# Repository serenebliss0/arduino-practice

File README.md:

# Arduino & Electronics Practice Repository

Welcome to my electronics learning journey! This repository contains both **Arduino microcontroller projects** and **pure electronic circuits** (without microcontrollers). Whether you're interested in programming or hardware design, you'll find projects here to expand your skills.

## 📁 Repository Structure

```
arduino-practice/
├── projects/               # All Arduino projects organized by category
│   ├── 01-basics/         # Fundamental Arduino concepts
│   ├── 02-sensors/        # Projects involving sensors
│   ├── 03-actuators/      # Projects with motors, servos, etc.
│   ├── 04-communication/  # Serial, I2C, SPI, Bluetooth, WiFi projects
│   ├── 05-displays/       # LCD, LED matrix, OLED projects
│   └── 06-advanced/       # Complex projects combining multiple concepts
|   └── 07-esp32           # ESP32 Centric projects
├── circuits/              # Pure electronic circuits (no microcontroller)
│   ├── 01-beginner/       # Basic circuits with ICs and transistors
│   ├── 02-intermediate/   # Multi-IC designs and complex logic
│   ├── 03-advanced/       # Advanced analog and digital circuits
│   └── schematics/        # Reference designs and datasheets
├── resources/             # Helpful resources, datasheets, and references
└── templates/             # Project templates and boilerplate code
```

## 🚀 Getting Started

### Prerequisites
- Arduino IDE (or Arduino CLI)
- Arduino board (Uno, Nano, Mega, etc.)
- USB cable for programming
- Basic electronic components (LEDs, resistors, breadboard, jumper wires)

### Setting Up
1. Install the [Arduino IDE](https://www.arduino.cc/en/software)
2. Connect your Arduino board via USB
3. Select the correct board and port in Arduino IDE
4. Open any project sketch (.ino file) and upload to your board

## 📚 Project Categories

### 01 - Basics
Learn fundamental Arduino concepts:
- Digital I/O (LEDs, buttons)
- Analog I/O (potentiometers, analog sensors)
- PWM (fading LEDs, simple motor control)
- Timing and delays
- Serial communication basics

### 02 - Sensors
Work with various sensors:
- Temperature sensors (DHT11, DHT22, LM35)
- Motion sensors (PIR, ultrasonic)
- Light sensors (LDR, photoresistor)
- Sound sensors
- Gas and smoke sensors

### 03 - Actuators
Control physical outputs:
- DC motors and motor drivers
- Servo motors
- Stepper motors
- Relays and solenoids
- Buzzers and speakers

### 04 - Communication
Connect and communicate:
- Serial (UART) communication
- I2C protocol
- SPI protocol
- Bluetooth modules (HC-05, HC-06)
- WiFi modules (ESP8266, ESP32)
- RF modules

### 05 - Displays
Visual output devices:
- 7-segment displays
- LCD displays (16x2, 20x4)
- OLED displays
- LED matrices
- RGB LEDs and LED strips

### 06 - Advanced
Complex integrated projects:
- IoT projects
- Data logging
- Home automation
- Robotics
- Multi-sensor systems

### 07- ESP32

ESP32 Centric projects:
 - Web Servers
 - Bluetooth Low Energy (LE)
 - WiFi Scanners
 - More IoT projects
 - OTA Updates

---

## ⚡ Electronic Circuits (No Microcontroller)

Learn electronics fundamentals by building circuits using ICs, transistors, and discrete components - **no programming required!** Perfect for understanding how hardware works at a deeper level.

### What's Included:
- **32+ Circuit Projects**: From beginner to advanced
- **Practical Learning**: 555 timers, op-amps, logic gates, counters, and more
- **Real Applications**: Amplifiers, power supplies, oscillators, sensors
- **Hardware Focus**: Pure analog and digital circuit design

### Why Learn Circuit Design?
- 🔹 **Understand Electronics Deeply**: See how components work together
- 🔹 **No Programming Needed**: Focus purely on hardware
- 🔹 **Complement Arduino Skills**: Better understand what Arduino does internally
- 🔹 **Build Useful Tools**: Power supplies, testers, amplifiers
- 🔹 **Lower Power**: Many circuits are more efficient than microcontrollers

### Circuit Categories:

#### Beginner (7 Projects)
- 555 Timer LED Blinker
- Dark-Activated LED (transistor switch)
- LED Chaser/Sequencer (4017 IC)
- Simple Audio Amplifier (LM386)
- Touch Switch
- And more!

#### Intermediate (12 Projects)
- SR Latch (Set-Reset Flip-Flop)
- Clap Switch (sound-activated)
- Adjustable Power Supply (LM317)
- Infrared Proximity Sensor
- Motor Speed Controller (PWM)
- Water Level Indicator
- Electronic Metronome (adjustable BPM)
- Capacitance Tester (identify unknown capacitors)
- LED Bar Graph Voltmeter
- And more!

#### Advanced (13 Projects)
- Function Generator (sine, square, triangle waves)
- Security Alarm System
- Digital Dice with 7-segment display
- Traffic Light Controller
- Stepper Motor Driver
- Temperature-Controlled Fan
- VU Meter (Audio Level Indicator)
- Infrared Remote Control System
- DC-DC Boost Converter (switch-mode power supply)
- And more!

### 📚 Full Documentation
For complete project descriptions, component lists, and learning resources:
- **[CIRCUITS.md](CIRCUITS.md)** - Comprehensive guide to all circuit projects
- **[circuits/README.md](circuits/README.md)** - Quick navigation and tips

### Getting Started with Circuits
1. Start with the 555 Timer LED Blinker (beginner)
2. Build the SR Latch to understand digital memory
3. Try an audio amplifier or LED chaser
4. Gradually move to intermediate and advanced projects

**Essential Component**: Get a **multimeter** if you don't have one - it's absolutely crucial for circuit building and debugging!

---

## 📝 How to Add a New Project

1. Choose the appropriate category folder
2. Create a new folder with a descriptive name (e.g., `blink-led`, `ultrasonic-distance`)
3. Add your Arduino sketch (.ino file)
4. Include a README.md with:
   - Project description
   - Components list
   - Circuit diagram or wiring instructions
   - Code explanation
   - Photos/videos of the working project (optional)

## 🛠️ Project Template

See the `templates/` folder for a basic project structure template.

## 📖 Resources

The `resources/` folder contains:
- Component datasheets
- Arduino cheat sheets
- Circuit diagrams
- Useful links and tutorials

## 💡 Need Project Ideas?

### Arduino Projects
Check out **[PROJECT_SUGGESTIONS.md](PROJECT_SUGGESTIONS.md)** for 50+ Arduino project ideas organized by difficulty level and category! Includes:
- Easy starter projects to build on what you've learned
- Intermediate projects combining multiple components
- Advanced IoT, robotics, and automation projects
- Recommended learning path
- Components shopping list

### Circuit Projects (No Microcontroller)
Check out **[CIRCUITS.md](CIRCUITS.md)** for 32+ pure electronics projects! Includes:
- Beginner circuits with 555 timers and basic ICs
- Intermediate circuits with op-amps and logic gates
- Advanced circuits with multiple ICs and complex designs
- Essential components guide
- Circuit design tips and learning resources

## 🛒 Shopping List

Need to buy parts? Check out **[SHOPPING_LIST.md](SHOPPING_LIST.md)** for a complete, consolidated shopping list covering **every component** needed for:
- All 32+ circuit projects (no microcontroller)
- All Arduino microcontroller projects
- All ESP32 projects

Organized by category (resistors, capacitors, ICs, sensors, etc.) with quantities, cost estimates, and sourcing tips so you can buy everything in one go.

## 🔗 Useful Links

- [Arduino Official Website](https://www.arduino.cc/)
- [Arduino Reference](https://www.arduino.cc/reference/en/)
- [Arduino Project Hub](https://create.arduino.cc/projecthub)
- [Arduino Forum](https://forum.arduino.cc/)

## 📜 License

This project is licensed under the MIT License - see the [LICENSE](LICENSE) file for details.

## 🤝 Contributing

This is a personal learning repository, but feel free to:
- Suggest improvements
- Share ideas for new projects
- Report issues or bugs in the code
- Visit the [Issues](https://github.com/serenebliss0/arduino-practice/issues) tab to suggest your idea or report an issue! 

---

Happy tinkering! 🎉

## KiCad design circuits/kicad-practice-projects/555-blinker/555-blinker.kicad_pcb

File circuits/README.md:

# 🔌 Circuits Directory

This directory contains electronic circuit projects that **don't require Arduino or any microcontroller**. These are pure hardware designs using ICs, transistors, and other discrete components.

## 📁 Directory Structure

```
circuits/
├── README.md                    # This file - navigation and overview
├── 01-beginner/                 # Basic circuits (7 projects)
│   ├── 01-555-timer-led-blinker/     ✅
│   ├── 02-simple-led-flashlight/     ✅
│   ├── 03-dark-activated-led/        ✅
│   ├── 04-push-button-debouncing/    ✅
│   ├── 05-simple-audio-amplifier/    ✅
│   ├── 06-led-chaser-4017/           ✅
│   └── 07-touch-switch/
├── 02-intermediate/             # Intermediate circuits (8 projects)
│   ├── 08-sr-latch/                  ✅
│   ├── 09-clap-switch/
│   ├── 10-automatic-emergency-light/
│   ├── 11-ir-proximity-sensor/
│   ├── 12-adjustable-power-supply/
│   ├── 13-motor-speed-controller/
│   ├── 14-water-level-indicator/
│   └── 15-bistable-relay/
├── 03-advanced/                 # Advanced circuits (11 projects)
│   ├── 16-digital-dice/
│   ├── 17-security-alarm-system/
│   ├── 18-traffic-light-controller/
│   ├── 19-function-generator/
│   ├── 20-dual-power-supply/
│   ├── 21-temperature-controlled-fan/
│   ├── 22-stepper-motor-driver/
│   ├── 23-digital-logic-probe/
│   ├── 24-analog-volt-ammeter/
│   ├── 25-pwm-motor-controller/
│   └── 26-binary-counter-7segment/
└── schematics/                  # General schematics and reference designs
```

## 🎯 What's in This Section?

### Project Organization
All 26 circuit projects from CIRCUITS.md are now organized into folders by difficulty level! Each project folder contains:
- **README.md**: Full documentation, theory, components, building instructions
- **Circuit files**: Fritzing (.fzz), schematics, and photos (as available)

### Current Status
- ✅ **All 26 project folders created** with documentation
- ✅ **Beginner projects (1-7)**: Complete READMEs with detailed instructions
- ✅ **Intermediate projects (8-9)**: Detailed READMEs, others have basic structure
- ✅ **Advanced projects (16-26)**: Basic structure with references to CIRCUITS.md
- ✅ **Existing circuits moved** to appropriate folders (555 Timer, SR Latch)

### Projects by Category

#### 01-Beginner/
- Basic circuits using LEDs, resistors, and simple ICs
- 555 timer projects
- Transistor switches
- Simple sensor circuits

#### 02-Intermediate/
- Multi-IC designs
- Op-amp circuits
- Counter and sequencer circuits
- Audio and power circuits

#### 03-Advanced/
- Complex state machines
- Multi-stage amplifiers
- Advanced timing circuits
- Power supplies and converters

#### Schematics/
- Reference designs
- Component datasheets
- Common circuit building blocks
- Test and measurement circuits

## 📚 Full Documentation

For complete project ideas, learning resources, and step-by-step guides, see:
- **[CIRCUITS.md](../CIRCUITS.md)** - Comprehensive guide with 26+ circuit projects
  - Beginner projects (7 projects)
  - Intermediate projects (9 projects)
  - Advanced projects (10 projects)
  - Component guides
  - Learning resources
  - Circuit design tips

## 🔨 How to Add New Circuit Projects

### 1. Choose the Right Category
- **Beginner**: Simple circuits with 1-2 ICs or basic transistor circuits
- **Intermediate**: Multi-IC designs, sensor integration, moderate complexity
- **Advanced**: Complex systems, multiple ICs, professional designs

### 2. Create Project Folder
```
circuits/[category]/project-name/
├── project-name.fzz           # Fritzing circuit file
├── schematic.png              # Exported schematic image
├── breadboard.png             # Breadboard layout (optional)
├── README.md                  # Project documentation
└── photos/                    # Working circuit photos
```

### 3. Document Your Circuit
Your README.md should include:

```markdown
# Project Name

## Difficulty: ⭐⭐⭐☆☆

## What You'll Learn
- Key concept 1
- Key concept 2
- Key concept 3

## Components Required
- Component 1 (quantity, specs)
- Component 2 (quantity, specs)
- etc.

## Circuit Description
Explain how the circuit works, what each section does.

## Theory of Operation
Detailed explanation of the circuit's operation.

## Building Instructions
1. Step 1
2. Step 2
3. etc.

## Testing & Troubleshooting
- Expected voltages at test points
- Common issues and solutions
- What to check if it doesn't work

## Photos
Include photos of your working circuit!

## Calculations
Any relevant formulas or calculations.

## Resources
- Links to datasheets
- Reference articles
- Tutorial videos
```

## 🛠️ Essential Tools & Components

### You Have / Likely Have:
- ✅ Breadboard
- ✅ Jumper wires
- ✅ Fritzing software

### Recommended Additions:
- [ ] **Multimeter** - Absolutely essential for circuit building!
- [ ] 555 Timer ICs - Most versatile IC ever
- [ ] Op-Amps (LM358 or LM324)
- [ ] Logic ICs (CD4017, CD4011)
- [ ] Basic transistors (BC547, TIP122)
- [ ] Assorted resistors and capacitors
- [ ] Power supply (breadboard power supply recommended)

## 📖 Getting Started

### New to Circuit Design?
1. Read [CIRCUITS.md](../CIRCUITS.md) for full project list
2. Start with beginner projects (#1-7)
3. Build the 555 Timer LED Blinker first
4. Learn to read datasheets
5. Practice on breadboard before soldering

### From Arduino to Circuits?
Great! You already understand:
- ✅ Basic electronics (voltage, current, resistance)
- ✅ Component identification
- ✅ How to use a breadboard
- ✅ Reading circuit diagrams

Now learn:
- 🔹 How ICs work at the hardware level
- 🔹 Analog circuit design
- 🔹 Timing and oscillator circuits
- 🔹 Digital logic without code
- 🔹 Power supply design

## 🎓 Learning Path

### Week 1-2: Start Simple
1. Build LED Blinker (555 timer)
2. Build SR Latch (understand flip-flops)
3. Experiment with component values

### Week 3-4: Add More ICs
4. LED Chaser (4017 counter)
5. Dark-Activated LED (transistor switch)
6. Touch Switch (logic gates)

### Week 5+: Intermediate & Beyond
Choose projects that interest you from CIRCUITS.md!

## 🔗 Useful Resources

### Circuit Simulators (Test Before Building!)
- **Falstad Circuit Simulator** - Browser-based, instant feedback
- **CircuitLab** - Online schematic capture and simulation
- **LTspice** - Professional SPICE simulator (free)

### Learning Sites
- **All About Circuits** - Free textbooks and tutorials
- **Electronics Tutorials** - Comprehensive circuit theory
- **EEVblog** - YouTube channel with electronics content

### Datasheets
Always check datasheets at:
- Manufacturer websites
- AllDataSheet.com
- DataSheetCatalog.com

## ⚡ Safety Reminders

### Always:
- ✅ Double-check polarity of electrolytic capacitors
- ✅ Verify IC pin 1 orientation (dot or notch)
- ✅ Use appropriate resistors for LEDs
- ✅ Add flyback diodes for inductive loads
- ✅ Check power supply voltage before connecting

### Never:
- ❌ Connect power backwards
- ❌ Exceed maximum ratings
- ❌ Touch live AC circuits
- ❌ Work on circuits while powered
- ❌ Skip the datasheet!

### For AC Projects:
- ⚠️ **DANGER**: AC voltage can be lethal
- ⚠️ Test with DC first
- ⚠️ Use proper insulation
- ⚠️ Turn off power at breaker
- ⚠️ Consider hiring an electrician for permanent installations

## 💡 Quick Tips

### Breadboarding:
- Use color-coded wires (Red=+5V, Black=GND, others=signals)
- Keep wires flat and organized
- Add 100nF bypass capacitors near each IC
- Route power rails carefully

### Debugging:
- Start with power - verify voltages first
- Check all connections visually
- Measure voltages at each IC pin
- Use LED indicators to trace signals
- Verify IC orientations (pin 1!)

### Components:
- Resistor color codes: Google "resistor color code calculator"
- Capacitor polarity: Longer leg = positive (for electrolytics)
- LED polarity: Longer leg = anode (+)
- IC pinout: Pin 1 has dot or notch, count counter-clockwise

## 🎯 Project Ideas by Goal

### Want to Learn Timing?
- 555 Timer LED Blinker
- LED Chaser (4017 + 555)
- PWM Motor Controller

### Want to Learn Logic?
- SR Latch
- Touch Switch
- Digital Dice
- Traffic Light Controller

### Want to Learn Analog?
- Audio Amplifier (LM386)
- Function Generator (Op-amps)
- Temperature-Controlled Fan
- Adjustable Power Supply

### Want to Build Something Useful?
- Clap Switch
- Emergency Light
- Water Level Indicator
- Security Alarm System

## 📝 Contributing

This is a personal learning repository, but you can:
- Suggest circuit project ideas
- Share improvements to existing circuits
- Report errors in schematics or documentation
- Recommend useful components or resources

---

## 🚀 Next Steps

1. **Read** [CIRCUITS.md](../CIRCUITS.md) for complete project descriptions
2. **Choose** a beginner project to start with
3. **Gather** components you need
4. **Build** on breadboard and document your work
5. **Test** thoroughly and troubleshoot
6. **Save** your Fritzing files here
7. **Document** your learning journey

---

**Remember**: Circuit design is a skill built through practice. Start simple, understand each component, and gradually tackle more complex projects. Every circuit you build adds to your knowledge!

Happy circuit building! ⚡🔧

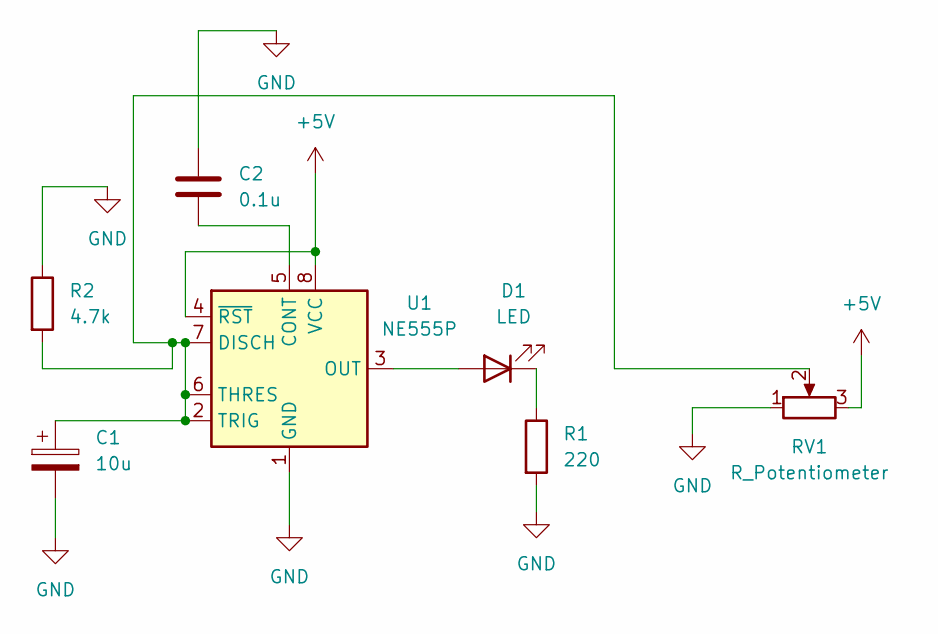
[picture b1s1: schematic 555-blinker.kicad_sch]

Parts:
C1: 10u; CP_Axial_L11.0mm_D6.0mm_P18.00mm_Horizontal
C2: 0.1u; C_Disc_D3.0mm_W1.6mm_P2.50mm
D1: LED; LED_D4.0mm
R1: 220; R_Axial_DIN0309_L9.0mm_D3.2mm_P15.24mm_Horizontal
R2: 4.7k; R_Axial_DIN0309_L9.0mm_D3.2mm_P15.24mm_Horizontal
RV1: R_Potentiometer; Potentiometer_Omeg_PC16BU_Horizontal
U1: NE555P; DIP-8_W7.62mm

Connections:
+5V: RV1.3, U1.4 (~RST), U1.8 (VCC)
GND: C1.2, C2.1, R1.2, R2.1, RV1.1, U1.1 (GND)
unnamed: D1.2 (A), U1.3 (OUT)
unnamed: D1.1 (K), R1.1
unnamed: C2.2, U1.5 (CONT)
unnamed: C1.1, R2.2, RV1.2, U1.2 (TRIG), U1.6 (THRES), U1.7 (DISCH)

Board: 2 copper layers, 7 parts (0 on the bottom side), 6 nets, no tracks yet.

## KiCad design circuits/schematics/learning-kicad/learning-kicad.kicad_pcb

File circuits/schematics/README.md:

# 📐 Schematics and Reference Designs

## Purpose
This directory contains general schematics, reference designs, and circuit building blocks that can be used across multiple projects.

## Contents

### Reference Circuits
- Common circuit building blocks
- Standard configurations for popular ICs
- Tested and verified designs

### Component Reference
- IC pinout diagrams
- Common component values
- Substitution guides

### Design Templates
- Power supply circuits
- Amplifier stages
- Filter circuits
- Oscillator designs
- Logic gate configurations

## Useful Reference Designs

### Power Supplies
- **5V Regulator (7805)**: Standard configuration with input/output caps
- **Variable Regulator (LM317)**: Adjustable voltage with calculation formulas
- **Dual Supply (±12V)**: Center-tapped transformer design

### Amplifiers
- **Common Emitter Amplifier**: Basic transistor amplifier stage
- **Op-Amp Configurations**: Inverting, non-inverting, differential
- **Audio Amp (LM386)**: Standard audio amplifier circuit

### Oscillators and Timers
- **555 Astable**: Basic oscillator with frequency calculations
- **555 Monostable**: One-shot timer configuration
- **Crystal Oscillator**: Precision timing circuits

### Logic and Digital
- **Debounce Circuit**: Clean switch inputs
- **SR Latch**: Basic flip-flop using gates
- **Clock Divider**: Using counter ICs

### Motor Control
- **H-Bridge**: Bidirectional motor control
- **Stepper Driver**: Unipolar and bipolar configurations
- **PWM Controller**: Variable speed control

### Sensors and Interfaces
- **LDR Light Sensor**: Light detection with threshold
- **Temperature Sensor**: LM35 interfacing
- **IR Transmitter/Receiver**: Proximity detection

## Adding Schematics

### File Formats
- **Fritzing (.fzz)**: For breadboard and schematic views
- **PDF**: For easy viewing and printing
- **PNG/JPG**: For quick reference
- **KiCad files**: For PCB design

### Naming Convention
```
[function]-[ic/component]-[variant].ext

Examples:
- 555-astable-1khz.fzz
- lm386-amplifier-min-gain.pdf
- 7805-regulator-standard.png
```

### Documentation
Each schematic should include:
1. **Title and description**
2. **Component values**
3. **Key formulas** (if applicable)
4. **Input/output specifications**
5. **Notes and warnings**

## Common IC Pinouts

### 555 Timer (8-pin DIP)
```
    +--U--+
GND |1   8| VCC
TRG |2   7| DIS
OUT |3   6| THR
RST |4   5| CTL
    +-----+
```

### LM358/LM324 Op-Amp
```
LM358 (Dual)        LM324 (Quad)
    +--U--+             +--U--+
1O  |1   8| VCC     1O  |1  14| 4O
1-  |2   7| 2O      1-  |2  13| 4-
1+  |3   6| 2-      1+  |3  12| 4+
GND |4   5| 2+      VCC |4  11| GND
    +-----+         2O  |5  10| 3+
                    2-  |6   9| 3-
                    2+  |7   8| 3O
                        +------+
```

### CD4017 Decade Counter
```
     +--U--+
 Q5  |1  16| VCC
 Q1  |2  15| RST
 Q0  |3  14| CLK
 Q2  |4  13| EN
 Q6  |5  12| OUT
 Q7  |6  11| Q4
 Q3  |7  10| Q8
 GND |8   9| Q9
     +------+
```

## Standard Component Values

### Resistors (E12 Series)
10, 12, 15, 18, 22, 27, 33, 39, 47, 56, 68, 82 (×10ⁿ)

Common values: 220Ω, 1kΩ, 10kΩ, 100kΩ, 1MΩ

### Capacitors
**Ceramic (nF)**: 1, 10, 100, 470
**Electrolytic (µF)**: 1, 10, 100, 470, 1000

### LEDs
- Forward Voltage: 1.8-3.6V (depending on color)
- Forward Current: 10-20mA (typical)
- Current Limiting Resistor: 220Ω - 1kΩ

## Circuit Design Tips

### Power Supply Guidelines
1. Always add 100nF bypass capacitor near each IC
2. Use electrolytic caps (10µF-100µF) for bulk filtering
3. Add reverse polarity protection (diode)
4. Calculate power dissipation for regulators
5. Use adequate heatsinks for power components

### Signal Conditioning
1. Use voltage dividers for scaling
2. Add RC filters for noise reduction
3. Buffer high-impedance signals with op-amps
4. Decouple analog and digital grounds

### Protection Circuits
1. Flyback diodes for inductive loads (motors, relays)
2. TVS diodes for ESD protection
3. Fuses for overcurrent protection
4. Zener diodes for voltage clamping

## Testing and Troubleshooting

### Essential Measurements
1. **Power rails**: Verify correct voltages
2. **IC pins**: Check VCC and GND first
3. **Signal paths**: Trace signals with multimeter/oscilloscope
4. **Component values**: Verify with multimeter

### Common Problems
- **No power**: Check connections and battery
- **Intermittent operation**: Loose connections
- **Incorrect output**: Wrong component values
- **Overheating**: Insufficient current limiting or heatsinking

## Resources

### Online Simulators
- **Falstad Circuit Simulator**: https://falstad.com/circuit/
- **CircuitLab**: https://www.circuitlab.com/
- **LTspice**: https://www.analog.com/en/design-center/design-tools-and-calculators/ltspice-simulator.html - Free SPICE simulator by Analog Devices

### Reference Websites
- **All About Circuits**: https://www.allaboutcircuits.com/
- **Electronics Tutorials**: https://www.electronics-tutorials.ws/
- **TI Precision Labs**: Training videos from Texas Instruments

### Datasheet Sources
- Manufacturer websites (TI, Analog, ON Semi, etc.)
- **AllDataSheet**: https://www.alldatasheet.com/
- **DataSheetCatalog**: https://www.datasheetcatalog.com/

## Contributing

### Adding New Schematics
1. Create clear, well-documented schematic
2. Test circuit on breadboard
3. Export in multiple formats (Fritzing, PDF, PNG)
4. Add README with full documentation
5. Include component list and values
6. Add notes about variations and alternatives

### Quality Guidelines
- ✅ Clean, readable schematic layout
- ✅ All components labeled with values
- ✅ Clear input/output labels
- ✅ Include test points
- ✅ Add notes for critical values
- ✅ Specify power requirements

## Safety Reminders

### Low Voltage Circuits (< 30V DC)
- ✅ Generally safe to touch
- ⚠️ Still respect polarity and component ratings

### High Voltage / AC Circuits
- ⚠️ **DANGEROUS** - Can be lethal!
- ⚠️ Never work on live AC circuits
- ⚠️ Use isolated transformers for testing
- ⚠️ Follow electrical codes for permanent installations
- ⚠️ Consider consulting qualified electrician

### Component Safety
- ⚠️ Watch capacitor polarity (can explode!)
- ⚠️ Use heatsinks for power components
- ⚠️ Don't exceed maximum IC voltages
- ⚠️ Add flyback diodes for relays/motors
- ⚠️ Fuse all power supplies

---

**Status**: 📋 Awaiting reference schematics and designs
**Last Updated**: December 2024

Build with confidence! 📐⚡

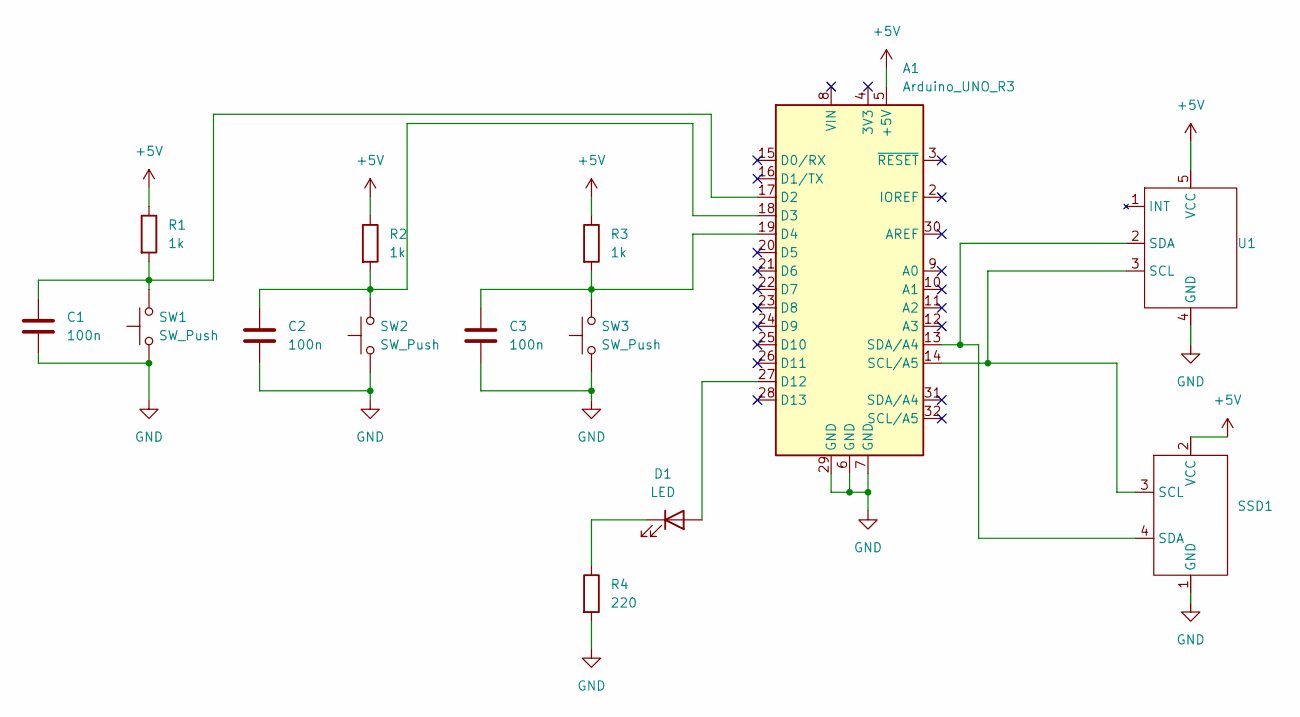
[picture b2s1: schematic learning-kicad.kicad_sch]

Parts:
A1: Arduino_UNO_R3
C1, C2, C3: 100n; C_Disc_D4.7mm_W2.5mm_P5.00mm
D1: LED; LED_D5.0mm
R1, R2, R3: 1k; R_Axial_DIN0207_L6.3mm_D2.5mm_P7.62mm_Horizontal
R4: 220; R_Axial_DIN0207_L6.3mm_D2.5mm_P7.62mm_Horizontal
SSD1: SSD1306
SW1, SW2, SW3: SW_Push; SW_PUSH_6mm
U1: MAX30102

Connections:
+5V: A1.5 (+5V), R1.1, R2.1, R3.1, SSD1.2 (VCC), U1.5 (VCC)
GND: A1.6 (GND), A1.7 (GND), A1.29 (GND), C1.2, C2.2, C3.2, R4.2, SSD1.1 (GND), SW1.1, SW2.1, SW3.1, U1.4 (GND)
unnamed: A1.17 (D2), C1.1, R1.2, SW1.2
unnamed: A1.18 (D3), C2.1, R2.2, SW2.2
unnamed: A1.19 (D4), C3.1, R3.2, SW3.2
unnamed: A1.27 (D12), D1.2 (A)
unnamed: D1.1 (K), R4.1
unnamed: A1.14 (SCL/A5), SSD1.3 (SCL), U1.3 (SCL)
unnamed: A1.13 (SDA/A4), SSD1.4 (SDA), U1.2 (SDA)

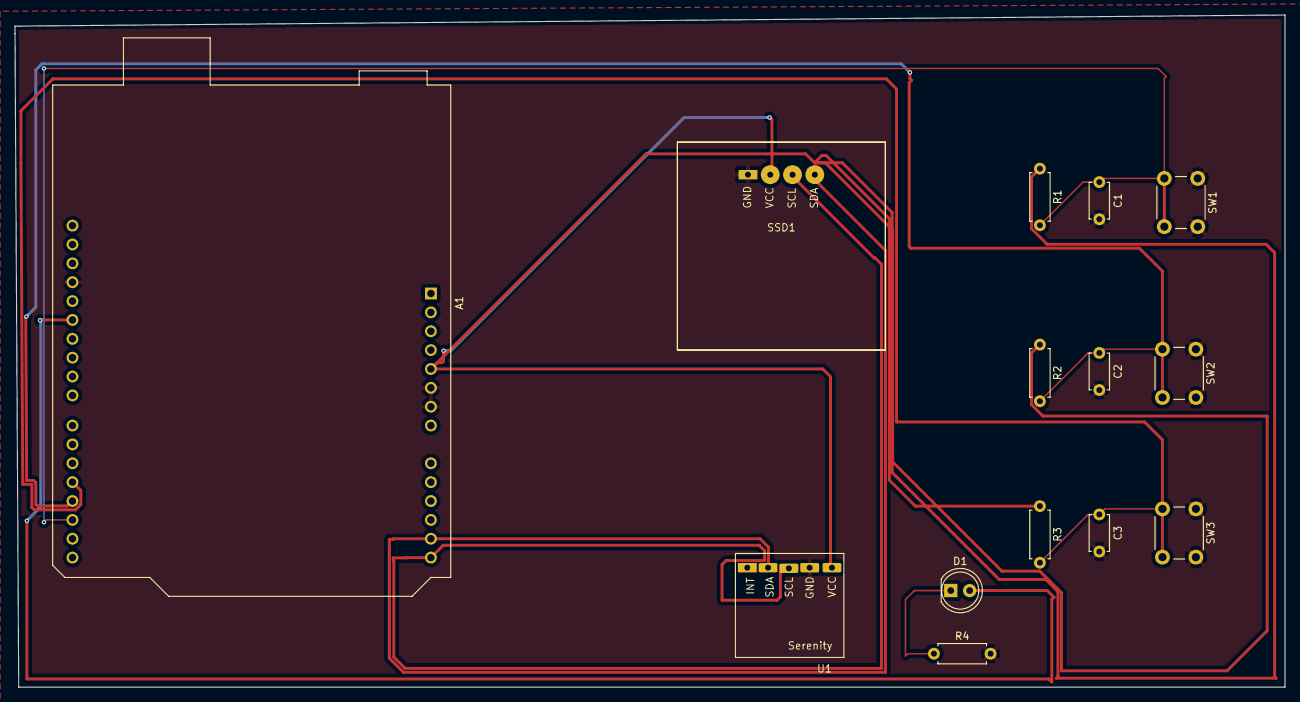
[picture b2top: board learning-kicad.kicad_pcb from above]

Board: 4 copper layers, 171.0 x 90.5 mm, 14 parts (0 on the bottom side), 9 nets.

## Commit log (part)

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2025-12-02 Initial plan
2025-12-02 Add comprehensive Arduino project organization structure
2025-12-02 Address code review feedback on documentation
2025-12-05 Added new projects
2025-12-07 Add comprehensive project suggestions with 50+ ideas
2025-12-07 Address code review feedback: clarify DHT sensors, safety warnings, I2C adapters, and ESP8266/ESP32
2025-12-07 Final refinements: complete sensor specs and clearer I2C/ESP explanations
2025-12-07 Implemented the Automatic Traffic Lights project using Arduino, featuring LED control based on ambient light detected by a photoresistor.
2025-12-07 Mark Traffic Light System project as completed
2025-12-07 Add new projects: LED arrays, PWM fading, and momentary switch; update project suggestions with completion status
2025-12-09 Add project files for LED Arrays, including code and Fritzing diagram
2025-12-10 Add comprehensive circuits section with 26+ projects
2025-12-11 Create complete circuit project folder structure with 26 projects
2025-12-11 Address code review feedback: fix emoji consistency and add LTspice URL
2025-12-11 Add Heads or Tails project with LED control and random number generation
2025-12-11 Add RGB LED color mixer project with button control and LED toggling
2025-12-13 Refactor code structure for improved readability and maintainability
2025-12-18 Mark RGB LED Color Mixer suggestion as completed
2025-12-18 Add RGB LED color mixer project with potentiometer control
2025-12-25 Finished dark activated led project
2025-12-25 Finished push button debouncing project
2025-12-26 Add simple reaction time game project
2025-12-27 Mark projects as completed in suggestions
2025-12-27 Update Easy Projects section with a checkmark
2025-12-29 Add DHT11 temperature and humidity sensor project with LCD display
    - Implemented a temperature sensor project using DHT11 sensor
    - Integrated 16x2 LCD display for real-time temperature and humidity readings
    - Established I2C communication for the LCD module
    - Included necessary libraries: Wire, LiquidCrystal_I2C, and DHTlib
    - Configured pin connections for DHT11 and LCD
    - Displayed temperature in Celsius and humidity percentage on the LCD
2025-12-29 Added a visual ultrasonic-sensor based distance measuring project
2025-12-31 Add comprehensive READMEs for projects 9 (Clap Switch) and 10 (Emergency Light)
2025-12-31 Add comprehensive READMEs for projects 11 (IR Sensor) and 12 (Power Supply)
2025-12-31 Add comprehensive READMEs for projects 13 (Motor Controller) and 14 (Water Level)
2025-12-31 Add comprehensive README for project 15 (Bistable Relay)
2025-12-31 Fix typo in project 15 README
2025-12-31 Add complete README files for projects 16 and 17
2025-12-31 Add complete README for project 18 (Traffic Light Controller)
2025-12-31 Add complete README for project 19 (Function Generator)
2025-12-31 Add complete README for project 20 (Dual Power Supply)
2026-02-06 Finished the LM386 Audio Amplifier project
2026-02-06 Added Audio Amplifier schematic
2026-02-06 Revise project status indicators in README
    Updated project status indicators for clarity.
2026-02-11 Add comprehensive README for ESP32 Email Notifier project
    - Created detailed 5,154-word README for project 05-email-notifier
    - Follows same format as project 04-mqtt-sensor-network
    - Includes all required sections: overview, components, wiring, code explanation, usage
    - Added detailed Gmail App Password setup instructions
    - Included SMTP configurations for Gmail, Outlook, and Yahoo
    - Comprehensive troubleshooting section for common SMTP and email issues
2026-02-11 Add comprehensive README for ESP32 OTA Updates project
2026-02-11 Add comprehensive NTP Clock project README with 5389 words
2026-02-11 Add comprehensive documentation and sketches for ESP32 projects 04-07
2026-02-11 Fix project reference in NTP Clock README
2026-02-11 Fix alignment in printDetailedInfo() function
2026-02-11 Add Project 10: BLE Beacon with comprehensive documentation and Arduino sketch
2026-02-11 Remove Arduino sketch files - keep documentation guides only
2026-02-14 Added new projects for ESP32 and started development on MAUI powered application for controlling via Bluetooth
2026-02-14 Add ESP32 projects section to README
    Added section for ESP32 centric projects with examples.
2026-02-21 Enhance README for LED chaser project
    Updated the README with additional details on the 555 Timer IC configuration, stability fixes, and circuit status.
2026-02-21 Update circuit status to completed
2026-02-21 Milestone Update – Embedded Systems Journey
    Completed:
    - CD4017 LED Chaser
    - ESP32 Web Server
    Started:
    - Learning KiCad (PCB design)
    - Google Assistant Smart Speaker project
2026-02-21 Removed unneccessary files
2026-02-21 Removed broken project
2026-02-22 Revise README for SR Latch circuit
    Updated the README to enhance clarity on SR Latch functionality and wiring instructions.
2026-02-22 Add SR Latch circuit schematic and started intermediate section in the circuits directory
2026-02-22 Added datasheet for CD4011
2026-02-25 Add 6 new projects, detailed guides for projects 21-26, and comprehensive shopping list
2026-02-26 Update README.md for clarity and suggestions
    Added a link to the Issues tab for suggestions and bug reports.
2026-02-26 Updated CIRCUITS.MD
    Added checkmarks to project difficulty ratings and linked to the shopping list.
2026-02-26 Update ESP32 setup instructions with PlatformIO
    Added installation instructions for PlatformIO and CH9102 driver.
2026-02-26 Updated shopping list
    Added more online stores and updated dates
2026-02-26 Expand README with PlatformIO usage instructions
    Added instructions for using PlatformIO in the README.
2026-02-27 Started learning PCB design
2026-03-14 Add backup zip file for KiCad learning and update Google Assistant project
2026-03-14 Started ESP32 Smart speaker project
2026-03-15 Added more features to esp32-smart-speaker project
2026-03-21 - Added more features to the wavelet speaker project - Fixed my .gitignore, again 😅
2026-03-21 Added more features to wavelet (esp32 smart speaker prject)
2026-04-18 Add esp32-smart-speaker as submodule
2026-04-19 Moved esp32-spk-project to its own repo and added as a submodule
2026-04-21 Added new projects and stuff : )
2026-06-24 Add esp32-keyboard project and new KiCad symbol library for TP4056
